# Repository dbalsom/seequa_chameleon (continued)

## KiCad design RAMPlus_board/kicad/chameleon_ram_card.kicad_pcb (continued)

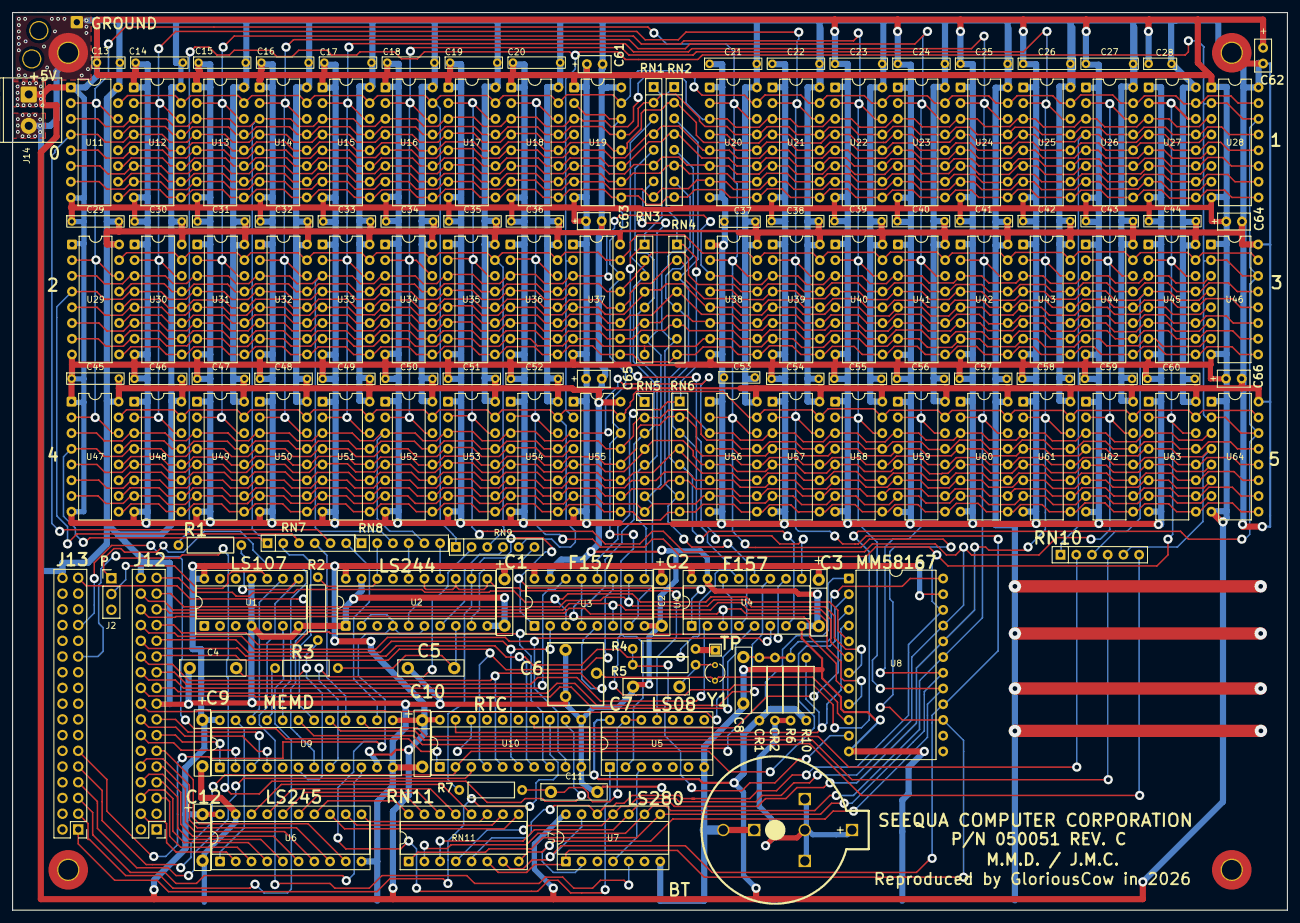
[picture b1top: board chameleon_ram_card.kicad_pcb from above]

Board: 2 copper layers, 206.0 x 145.0 mm, 165 parts (0 on the bottom side), 133 nets.

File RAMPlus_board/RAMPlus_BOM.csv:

"Reference","seq_silkscreen","Qty","Value","seq_partno","Description","seq_socket","seq_purchase_url","Datasheet","DNP","Exclude from BOM","Exclude from Board"
"U7","LS280","1","SN74LS280N","SN74LS280N","LS280 Parity Generator","","https://www.mouser.com/ProductDetail/Texas-Instruments/SN74L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","http://www.ti.com/lit/gpn/sn74LS280","","",""
"J14","","1","Screw_Terminal_01x02","","Any screw terminal with 5mm pitch","","https://www.mouser.com/ProductDetail/Wurth-Elektronik/691137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","https://www.we-online.com/components/products/datasheet/6911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","","",""
"J2","","1","PARITY","Pin header, Vertical, 1x3, 2.54mm pitch","Generic 2.54mm 1x3 pin header","","","~","","",""
"U9","MEMD","1","PAL20L10","","Programmable Array Logic (PAL), Active-Low Combinatorial, DIP-24","DIP-24","","https://rocelec.widen.net/view/pdf/pn0qtf2whd/VANTS00076-1.pdf","","",""
"U10","RTC","1","PAL16R4","","Programmable Array Logic (PAL), Active-Low Combinatorial, DIP-20 / PLCC-20","DIP-20","","https://www.alldatasheet.com/datasheet-pdf/download/55543/AM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","","",""
"U8","MM58167","1","MM58167","MM58167AN /B8348","Microprocessor Real Time Clock, CMOS","DIP-24","https://www.ebay.com/sch/i.html?_nkw=MM58167AN","https://www.futurlec.com/Others/MM58167AN.shtml","","",""
"U11,U12,U13,U14,U15,U16,U17,U18,U19,U20,U21,U22,U23,U24,U25,U26,U27,U28,U29,U30,U31,U32,U33,U34,U35,U36,U37,U38,U39,U40,U41,U42,U43,U44,U45,U46,U47,U48,U49,U50,U51,U52,U53,U54,U55,U56,U57,U58,U59,U60,U61,U62,U63,U64","","54","MK4564","Mostek MK4564N-20","65536 x 1 bit Dynamic RAM, 120/150ns access time, single 5V ±10% power supply, TTL compatible inputs, DIP-16 (Epoxy/Plastic package)","DIP-16","https://www.electronicsurplus.com/mostek-mk4564n15-ic-memory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","https://www.minuszerodegrees.net/memory/4164/datasheet_MK456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","","",""
"J13","","1","Expansion Header J13","Pin header, Vertical, 2x17, 2.54mm pitch","Seequa Chameleon Expansion Header J13 - Signal Pins","","","~","","",""
"J12","","1","Expansion Header J12","Pin header, Vertical,  2x17, 2.54mm pitch","Seequa Chameleon Expansion Header J12 - Data and Address pins","","","~","","",""
"U6","LS245","1","74LS245","SN74LS245N","Octal BUS Transceivers, 3-State outputs","DIP-20","https://www.mouser.com/ProductDetail/Texas-Instruments/SN74L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","http://www.ti.com/lit/gpn/sn74LS245","","",""
"U2","LS244","1","74LS244","Mitsubishi M74LS244P ","Octal Buffer and Line Driver With 3-State Output, active-low enables, non-inverting outputs","DIP-20","https://www.mouser.com/ProductDetail/Texas-Instruments/SN74L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","http://www.ti.com/lit/ds/symlink/sn74ls244.pdf","","",""
"U1","LS107","1","74LS107","Mitsubishi M74LS107AP 812600","Dual JK Flip-Flop, reset","DIP-14","https://www.mouser.com/ProductDetail/Texas-Instruments/SN74L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","http://www.ti.com/lit/gpn/sn74LS107","","",""
"U5","LS08","1","74LS08","Mitsubishi M74LS08P 831300","Quad And2","DIP-14","https://www.mouser.com/ProductDetail/Texas-Instruments/SN74L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","http://www.ti.com/lit/gpn/sn74LS08","","",""
"U3,U4","F157","2","74F157","74F157N K8351","Quad 2 to 1 line Multiplexer","DIP-16","https://www.mouser.com/ProductDetail/Texas-Instruments/SN74F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","https://www.ti.com/lit/ds/symlink/sn74f157a.pdf?ts=1772755109970","","",""
"C6","","1","5.0 - 70.0pF","Johanson 9338","Differential variable capacitor with two stators","","https://www.surplussales.com/items/106928/ceramic-trimmer-ca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 ","https://surplussales-prod-media.sfo3.digitaloceanspaces.com/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","","",""
"CR1,CR2","","2","1N4148","","100V 0.15A standard switching diode, DO-35","","https://www.mouser.com/ProductDetail/Diotec-Semiconductor/1N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","https://assets.nexperia.com/documents/data-sheet/1N4148_1N4448.pdf","","",""
"R2,R3,R7","","3","510Ω","","Resistor,Resistor, small symbol","","","~","","",""
"RN10","","1","330Ω","6Y331Q Resistor Pack","3 resistor network, parallel topology, SIP package, split","","https://www.mouser.com/ProductDetail/Bourns/4606X-102-331LF?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","https://www.mouser.com/datasheet/3/40/1/4600x.pdf","","",""
"RN7,RN8","","2","330Ω","6Y331Q Resistor Pack","3 resistor network, parallel topology, SIP package, split","","https://www.mouser.com/ProductDetail/Bourns/4606X-102-331LF?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","https://www.mouser.com/datasheet/3/40/1/4600x.pdf","","",""
"RN1,RN2,RN3,RN4,RN5,RN6","","6","330Ω","4308R-120-330","4 resistor network, parallel topology, SIP package","","https://www.mouser.com/ProductDetail/Bourns/4308R-102-331LF?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","https://www.mouser.com/datasheet/3/40/1/4300R.pdf","","",""
"R1","","1","300Ω","","Standard THT Resistor, 1/4 watt, ±5%","","","~","","",""
"RN9","","1","270Ω","DALE 3-271G 8504","3 resistor network, parallel topology, SIP package, split","","https://www.mouser.com/ProductDetail/Bourns/4606X-102-271LF?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","https://www.mouser.com/datasheet/3/40/1/4600x.pdf","","",""
"R5","","1","200kΩ","","Standard THT Resistor, 1/4 watt, ±5%","","","~","","",""
"RN11","","1","180Ω","","8 resistor network, parallel topology","DIP-16","https://www.mouser.com/ProductDetail/Bourns/4116R-1-181LF?qs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","https://www.mouser.com/datasheet/3/40/1/4100R.pdf","","",""
"C11","","1","82pF*","39K U2J 1KV","Unpolarized, dipped ceramic filter capacitor, ±10% 1KV","","","~","","",""
"Y1","","1","32.768 kHz","Unmarked","Two pin crystal, can, standard clock freq 32.768 kHz","","https://www.mouser.com/ProductDetail/ABRACON/AB38T-32.768KHZ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","https://www.mouser.com/datasheet/3/184/1/AB38T.pdf","","",""
"BT1","BT","1","3V Lithium","CR2032 Coin Cell holder, P20.8mm","Single-cell battery, CR2032","","https://www.mouser.com/ProductDetail/Eagle-Plastic-Devices/1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","https://www.mouser.com/catalog/specsheets/EPD-200880.pdf","","",""
"R10","","1","2kΩ","","Standard THT Resistor, 1/4 watt, ±5%","","","~","","",""
"R6","","1","1.6MΩ","","Flame-proof resistor, 1/4 watt, ±5%","","","~","","",""
"R4","","1","1MΩ","","Flame-proof resistor, 1/4 watt, ±5%","","","~","","",""
"C8","","1","0.1µF","","Unpolarized, dipped film bypass capacitor","","","~","","",""
"C1,C2,C3,C9,C10,C12","","6","0.1uF","","0.1uF Dipped Tantalum, 35V","","","~","","",""
"C61,C62,C63,C64,C65,C66","","6","0.1µF","","0.1uF Dipped Tantalum, 35V","","","~","","",""
"C37,C53","","2","0.1µF","","0.1uF Dipped Film, ±10%","","","~","","",""
"C14,C15,C16,C17,C18,C19,C20,C21,C22,C23,C24,C25,C26,C27,C29,C30,C31,C32,C33,C34,C35,C36,C38,C39,C40,C41,C42,C43,C44,C45,C46,C47,C48,C49,C50,C51,C52,C54,C55,C56,C57,C58,C59,C60","","44","0.1µF","","0.1uF Dipped Film, ±10%","","","~","","",""
"C13,C28","","2","0.1µF","","0.1uF Dipped Film, ±10%","","","~","","",""
"C4,C5","","2","39pF","39K U2J 1KV","Unpolarized, dipped ceramic filter capacitor, ±10% 1KV","","","~","","",""
"C7","","1","20pF","20K S2L 1KV","Unpolarized dipped ceramic disk capacitor, ±10%, 1KV","","","~","","",""

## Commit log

2026-02-20 Initial upload
2026-02-20 exclude subdirs of src
2026-02-20 add readme
2026-02-20 add image link
2026-02-20 add link to kicad
2026-02-20 Fixes to clocks, keyboard controller stuff.
2026-02-23 update kicad project
2026-02-26 More updates
2026-02-28 Add parallel port, game port
2026-03-06 Add RAMPlus board
2026-05-13 Updates, chameleon logo
2026-05-13 A little work on composite output and GPIB
2026-06-09 Clean up RAMPlus board post migration
